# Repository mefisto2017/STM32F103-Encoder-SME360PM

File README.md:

# STM32F103-Encoder-SME360PM

> __Warning__
 Crystal oscilator pins are not connected, working on the fix!

## About The Project
The code and board schematic were designed to read 4 absolute encoders SME360PM of a 4 wheel independent steering robot and transmit the values through CAN interface. The values are read in continous mode and organized using DMA. The board is based on the STM32F103 blue pill.

## Getting Started

1. To request the values the following message must be send:
```sh
  [0x01, 0x00, 0x00, 0x00, 0x42, 0x1, 0x00, 0x00, 0x00, 0x00, 0x00, 0x00, 0x00]
```

2. The python script can be use to read and decode the angles 
```sh
  python3 Python_test_code/test.py
```

## Schematic Files
Schematic and gerber were generated on Eagle.

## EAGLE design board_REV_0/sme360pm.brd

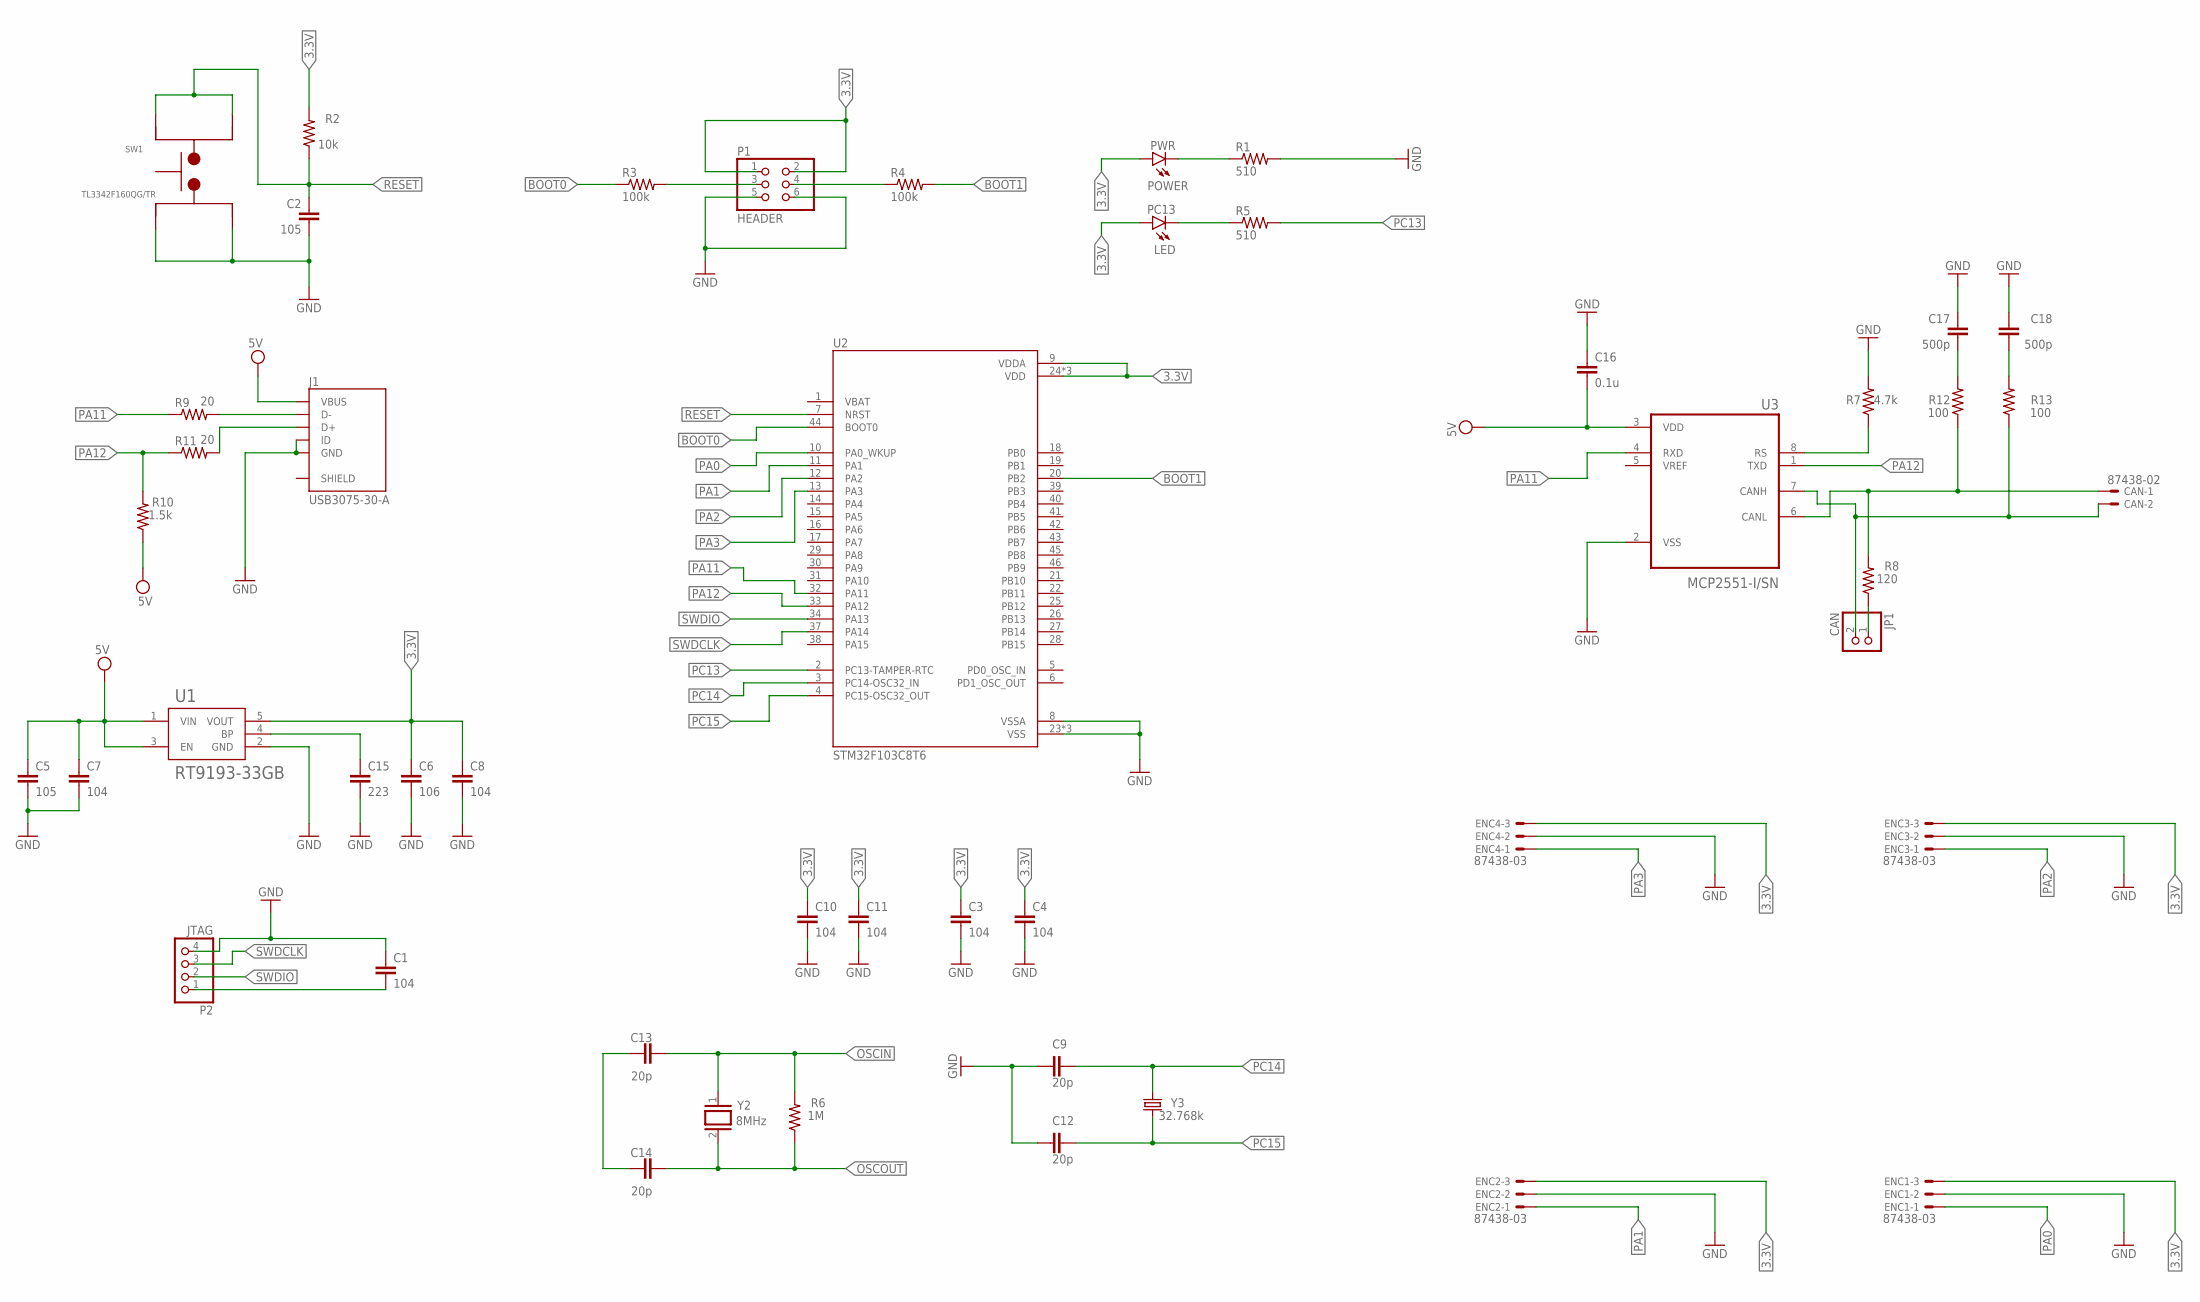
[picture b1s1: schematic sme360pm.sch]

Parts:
C1, C3, C4, C7, C8, C10, C11: 104; C0603
C2: 105; C0603
C5: 105; C0805
C6: 106; C0805
C9, C12, C13, C14: 20p; C0603
C15: 223; C0603
C16: 0.1u; C0603
C17, C18: 500p; C0603
CAN: 87438-02
ENC1, ENC2, ENC3, ENC4: 87438-03
J1: USB3075-30-A; GCT_USB3075-30-A
JP1: CAN; 1X02
P1: HEADER; 2X03
P2: JTAG; 1X04
PC13: LED; CHIP-LED0603
PWR: POWER; CHIP-LED0603
R1, R5: 510; R0603
R2: 10k; R0603
R3, R4: 100k; R0603
R6: 1M; R0603
R7: 4.7k; R0603
R8: 120; R0805
R9, R11: 20; R0603
R10: 1.5k; R0603
R12, R13: 100; R0603
SW1: TL3342F160QG/TR; SW_TL3342F160QG/TR
U1: RT9193-33GB; SOT94P279X129-5N
U2: STM32F103C8T6; QFP50P900X900X160-48N
U3: MCP2551-I/SN; SOIC127P599X175-8N
Y2: 8MHz; QS
Y3: 32.768k; 8.2X3.8

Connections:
3.3V: C3.1, C4.1, C6.1, C8.1, C10.1, C11.1, ENC1.3, ENC2.3, ENC3.3, ENC4.3, P1.1, P1.2, PC13.A, PWR.A, R2.2, U1.5 (VOUT), U2.9 (VDDA), U2.24 (VDD), U2.36 (VDD), U2.48 (VDD)
BOOT0: R3.1, U2.44 (BOOT0)
BOOT1: R4.2, U2.20 (PB2)
GND: C1.1, C2.1, C3.2, C4.2, C5.2, C6.2, C7.2, C8.2, C9.2, C10.2, C11.2, C12.2, C15.2, C16.1, C17.2, C18.2, ENC1.2, ENC2.2, ENC3.2, ENC4.2, J1.4 (ID), J1.5 (GND), P1.5, P1.6, P2.4, R1.2, R7.2, SW1.1, SW1.2, U1.2 (GND), U2.8 (VSSA), U2.23 (VSS), U2.35 (VSS), U2.47 (VSS), U3.2 (VSS)
unnamed: J1.2 (D-), R9.2
unnamed: J1.3 (D+), R11.2
unnamed: PWR.C, R1.1
unnamed: C15.1, U1.4 (BP)
unnamed: C13.1, C14.1
unnamed: PC13.C, R5.1
unnamed: C1.2, P2.1
unnamed: P1.3, R3.2
unnamed: P1.4, R4.1
unnamed: R7.1, U3.8 (RS)
unnamed: CAN.1, R8.2, R12.1, U3.6 (CANL)
unnamed: JP1.1, R8.1
unnamed: CAN.2, JP1.2, R13.1, U3.7 (CANH)
unnamed: C17.1, R12.2
unnamed: C18.1, R13.2
OSCIN: C13.2, R6.2, Y2.1
OSCOUT: C14.2, R6.1, Y2.2
PA0: ENC1.1, U2.10 (PA0_WKUP)
PA1: ENC2.1, U2.11 (PA1)
PA2: ENC3.1, U2.12 (PA2)
PA3: ENC4.1, U2.13 (PA3)
PA11: R9.1, U2.32 (PA11), U3.4 (RXD)
PA12: R10.2, R11.1, U2.33 (PA12), U3.1 (TXD)
PC13: R5.2, U2.2 (PC13-TAMPER-RTC)
PC14: C9.1, U2.3 (PC14-OSC32_IN), Y3.4 (2)
PC15: C12.1, U2.4 (PC15-OSC32_OUT), Y3.1
RESET: C2.2, R2.1, SW1.3, SW1.4, U2.7 (NRST)
SWDCLK: P2.3, U2.37 (PA14)
SWDIO: P2.2, U2.34 (PA13)
VCC: C5.1, C7.1, C16.2, J1.1 (VBUS), R10.1, U1.1 (VIN), U1.3 (EN), U3.3 (VDD)

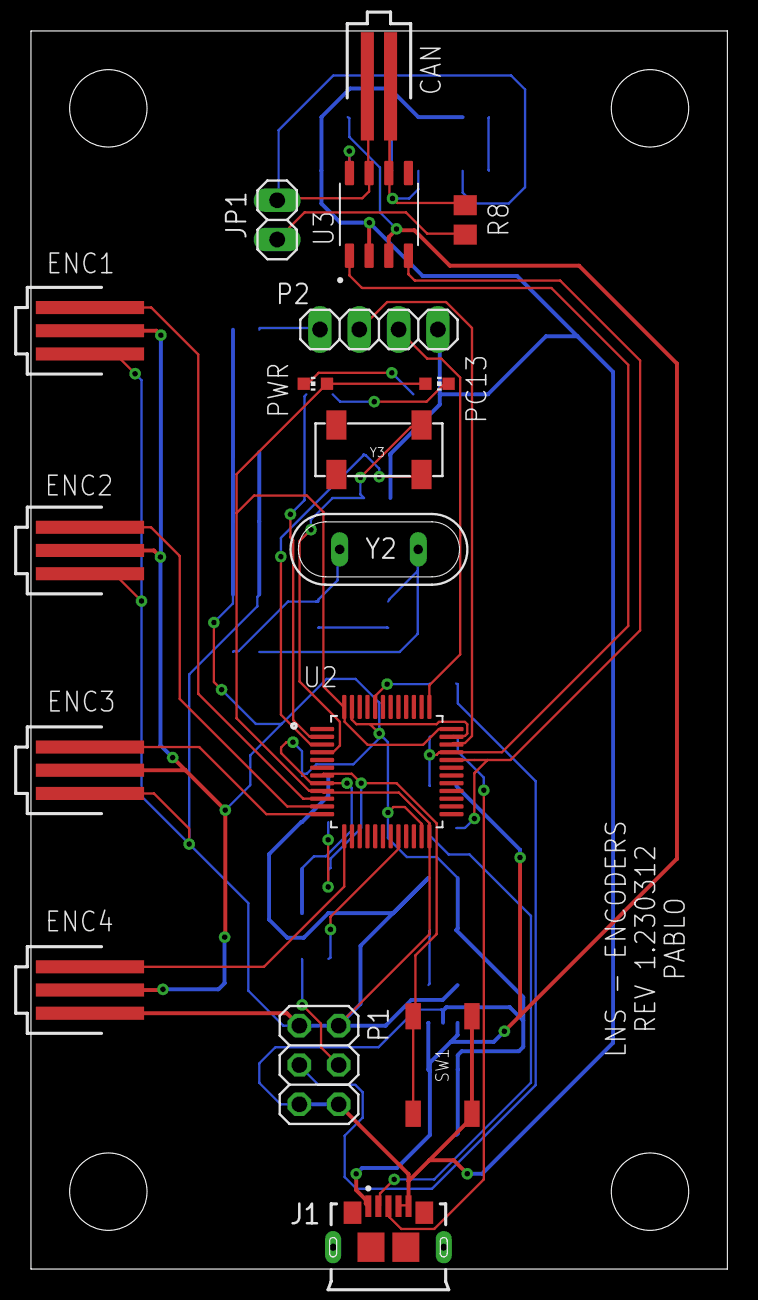
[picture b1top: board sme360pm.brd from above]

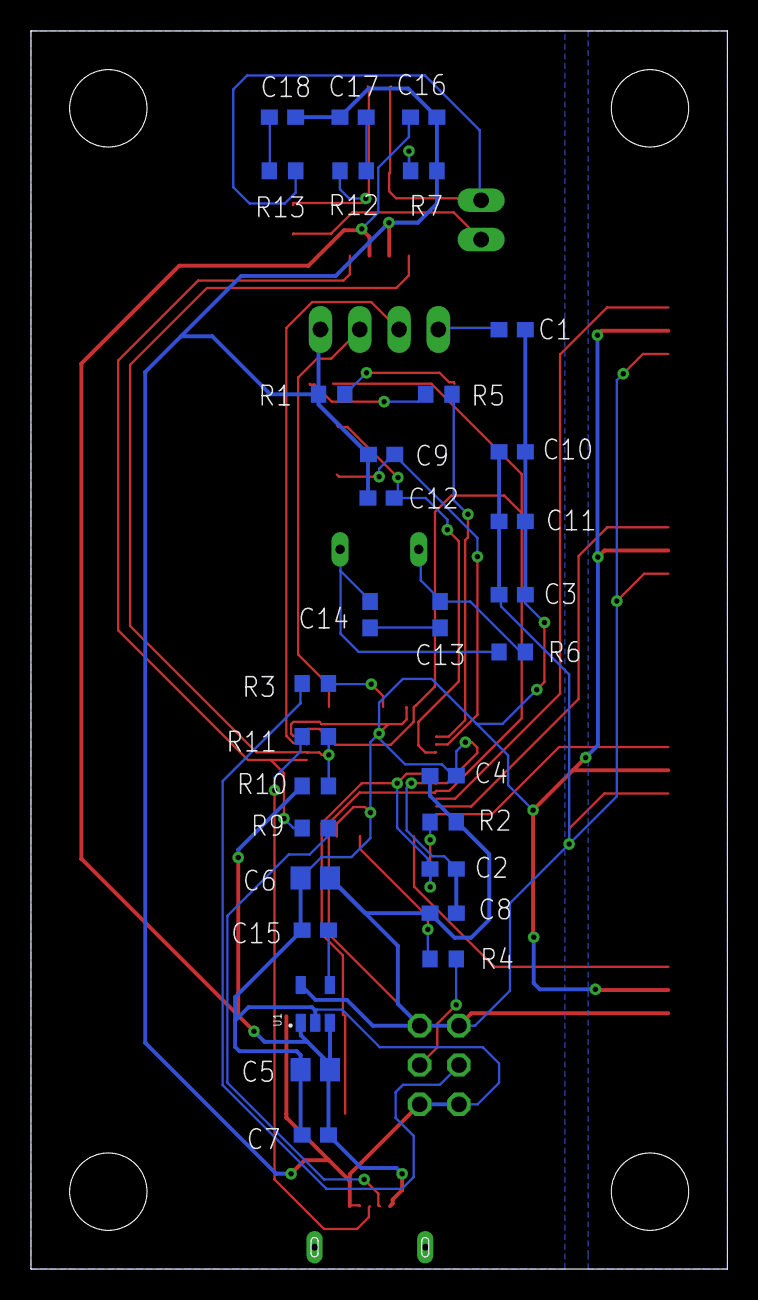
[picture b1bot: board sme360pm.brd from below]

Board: 2 copper layers, 45.0 x 80.0 mm, 48 parts (31 on the bottom side), 34 nets.

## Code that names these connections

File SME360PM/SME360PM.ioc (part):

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Mcu.Name=STM32F103C(8-B)Tx
Mcu.Package=LQFP48
Mcu.UserName=STM32F103C8Tx
PA0-WKUP.Signal=ADCx_IN0
PA1.Signal=ADCx_IN1
PA11.Mode=CAN_Activate
PA11.Signal=CAN_RX
PA12.Mode=CAN_Activate
PA12.Signal=CAN_TX
PA13.Mode=Serial_Wire
PA13.Signal=SYS_JTMS-SWDIO
PA14.Mode=Serial_Wire
PA14.Signal=SYS_JTCK-SWCLK
PA2.Signal=ADCx_IN2
PA3.Signal=ADCx_IN3
PD0-OSC_IN.Mode=HSE-External-Oscillator
PD0-OSC_IN.Signal=RCC_OSC_IN
PD1-OSC_OUT.Mode=HSE-External-Oscillator
PD1-OSC_OUT.Signal=RCC_OSC_OUT
RCC.SYSCLKFreq_VALUE=72000000
RCC.SYSCLKSource=RCC_SYSCLKSOURCE_PLLCLK
board=custom

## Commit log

2023-02-26 STM project creation
2023-02-27 added CAN code
2023-03-02 ADC DMA
2023-03-04 Board eagle files
2023-03-06 Updated board
2023-03-09 CAN example
2023-03-09 check communication and values
    using socket and CANET200
2023-03-09 STM32 code
2023-03-09 Fix problem values coupled
2023-03-11 Removed voltage divider
2023-03-13 Added adc prescaler value
2023-04-02 gerber files
2023-04-02 typo
2023-04-02 license

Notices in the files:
parts and their libraries:
crystal-geyer_V1_0: Copyright: Geyer-Electronic
